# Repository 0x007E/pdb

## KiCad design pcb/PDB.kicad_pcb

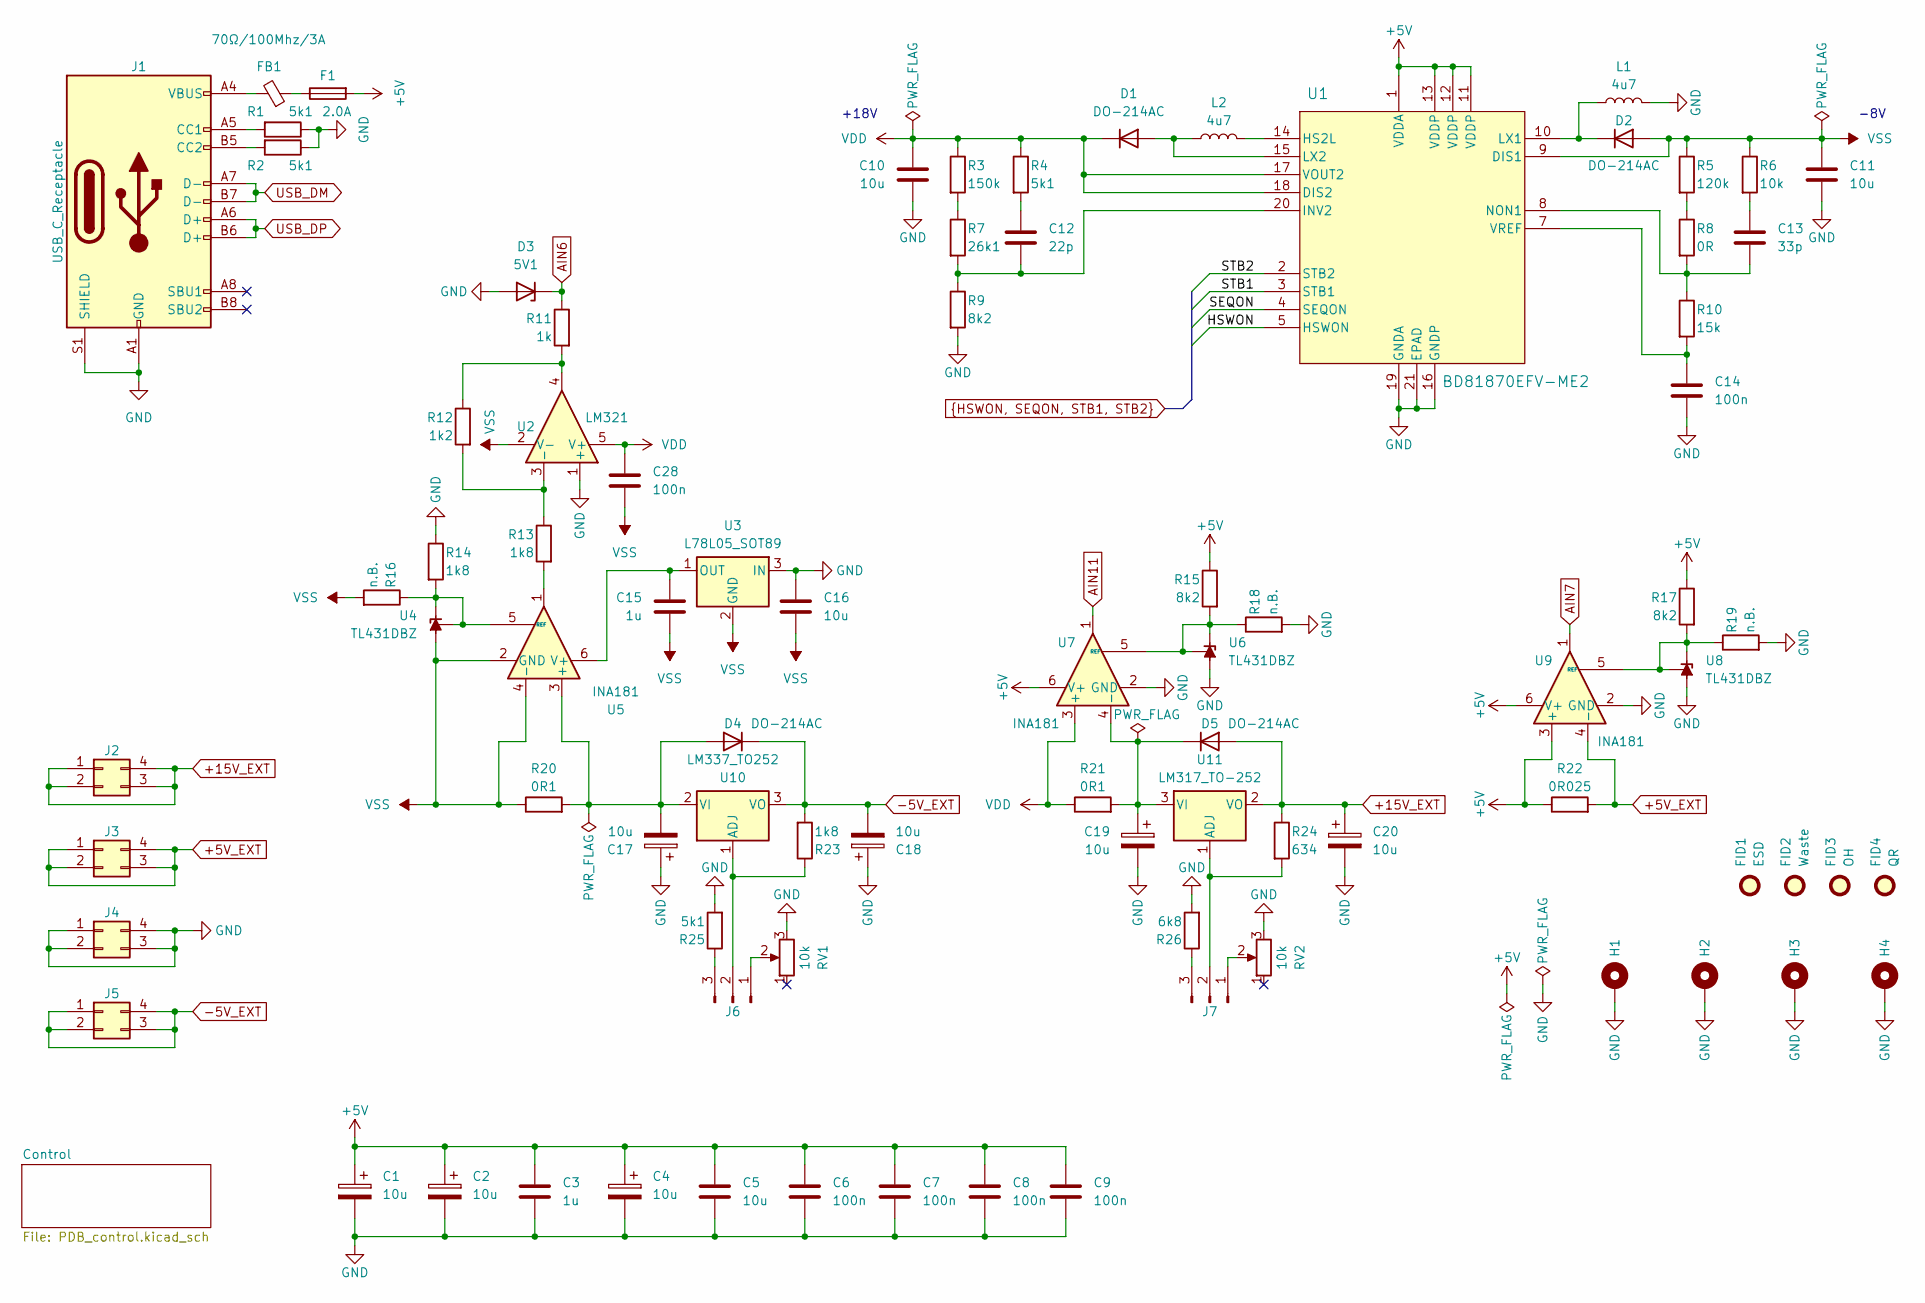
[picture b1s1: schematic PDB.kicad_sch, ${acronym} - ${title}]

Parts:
C1, C2, C4, C17, C18, C19, C20: 10u; CP_Elec_6.3x5.9; DigiKey 732-8545-1-ND
C3, C15: 1u; C_1206_3216Metric
C5, C10, C11, C16: 10u; C_1206_3216Metric
C6, C7, C8, C9, C14, C28: 100n; C_1206_3216Metric
C12: 22p; C_1206_3216Metric
C13: 33p; C_1206_3216Metric
D1, D2, D4, D5: DO-214AC; D_SMA
D3: 5V1; D_MiniMELF
F1: 2.0A; Fuse_1206_3216Metric
FB1: 70Ω/100Mhz/3A; L_1206_3216Metric
FID1: ESD; ESD-Logo_6.6x6mm_SilkScreen
FID2: Waste; WEEE-Logo_4.2x6mm_SilkScreen
FID3: OH; OSHW-Logo_5.7x6mm_SilkScreen
FID4: QR; QR_0x007e
H1, H2, H3, H4: MountingHole_Pad; MountingHole_3.2mm_M3_Pad
J1: USB_C_Receptacle; USB_C_Receptacle_GCT_USB4110
J2, J3, J4, J5: Conn_02x02_Counter_Clockwise; PinSocket_2x02_P2.54mm_Vertical; DigiKey 2057-RS2-04-G-ND
J6, J7: Conn_01x03_Pin; PinHeader_1x03_P2.54mm_Vertical
L1, L2: 4u7; L_Taiyo-Yuden_NR-40xx; DigiKey 587-2893-1-ND
R1, R2, R4, R25: 5k1; R_1206_3216Metric
R3: 150k; R_1206_3216Metric
R5: 120k; R_1206_3216Metric
R6: 10k; R_1206_3216Metric
R7: 26k1; R_1206_3216Metric
R8: 0R; R_1206_3216Metric
R9, R15, R17: 8k2; R_1206_3216Metric
R10: 15k; R_1206_3216Metric
R11: 1k; R_1206_3216Metric
R12: 1k2; R_1206_3216Metric
R13, R14, R23: 1k8; R_1206_3216Metric
R16, R18, R19: n.B.; R_1206_3216Metric
R20, R21: 0R1; R_2010_5025Metric; DigiKey CRM2010-FX-R100ELFCT-ND
R22: 0R025; R_2010_5025Metric
R24: 634; R_1206_3216Metric
R26: 6k8; R_1206_3216Metric
RV1, RV2: 10k; Potentiometer_Bourns_3296W_Vertical
U1: BD81870EFV-ME2; HTSSOP-20-1EP_4.4x6.5mm_P0.65mm_EP2.85x4mm; DigiKey BD81870EFV-ME2CT-ND
U2: LM321; SOT-23-5; DigiKey LM321SN3T1GOSCT-ND
U3: L78L05_SOT89; SOT-89-3
U4, U6, U8: TL431DBZ; SOT-23; DigiKey 5399-TL431CT-ND
U5, U7, U9: INA181; SOT-23-6
U10: LM337_TO252; TO-252-2; DigiKey 296-21578-1-ND
U11: LM317_TO-252; TO-252-2; DigiKey 5272-LM317MDT-EVCT-ND

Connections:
+5V: C1.1, C2.1, C3.1, C4.1, C5.1, C6.1, C7.1, C8.1, C9.1, F1.2, R15.1, R17.1, R22.1, U1.1 (VDDA), U1.11 (VDDP), U1.12 (VDDP), U1.13 (VDDP), U7.6 (V+), U9.3 (+), U9.6 (V+); also elsewhere on the board
+5V_EXT: J3.1, J3.2, J3.3, J3.4, R22.2, U9.4 (-); also elsewhere on the board
+15V_EXT: C20.1, D5.2 (A), J2.1, J2.2, J2.3, J2.4, R24.1, U11.2 (VO); also elsewhere on the board
-5V_EXT: C18.2, D4.1 (K), J5.1, J5.2, J5.3, J5.4, R23.2, U10.3 (VO); also elsewhere on the board
AIN6: D3.1 (K), R11.1; also elsewhere on the board
AIN7: U9.1; also elsewhere on the board
AIN11: U7.1; also elsewhere on the board
GND: C1.2, C2.2, C3.2, C4.2, C5.2, C6.2, C7.2, C8.2, C9.2, C10.1, C11.1, C14.1, C16.2, C17.1, C18.1, C19.2, C20.2, D3.2 (A), H1.1, H2.1, H3.1, H4.1, J1.A1 (GND), J1.A12 (GND), J1.B1 (GND), J1.B12 (GND), J1.S1 (SHIELD), J4.1, J4.2, J4.3, J4.4, L1.2, R1.1, R2.1, R9.2, R14.1, R18.2, R19.2, R25.2, R26.2, RV1.3, RV2.3, U1.16 (GNDP), U1.19 (GNDA), U1.21 (EPAD), U2.1 (+), U3.3 (IN), U6.3 (A), U7.2 (GND), U8.3 (A), U9.2 (GND); also elsewhere on the board
HSWON: U1.5 (HSWON); also elsewhere on the board
unnamed: C12.1, R4.2
unnamed: C13.2, R6.2
unnamed: D1.2 (A), L2.1, U1.15 (LX2)
unnamed: D2.1 (K), L1.1, U1.10 (LX1)
unnamed: C17.2, D4.2 (A), R20.2, U5.3 (+), U10.2 (VI)
unnamed: C19.1, D5.1 (K), R21.2, U7.4 (-), U11.3 (VI)
unnamed: F1.1, FB1.1
unnamed: FB1.2, J1.A4 (VBUS), J1.A9 (VBUS), J1.B4 (VBUS), J1.B9 (VBUS)
unnamed: J1.A5 (CC1), R1.2
unnamed: J1.B5 (CC2), R2.2
unnamed: J6.1, RV1.2
unnamed: J6.2, R23.1, U10.1 (ADJ)
unnamed: J6.3, R25.1
unnamed: J7.1, RV2.2
unnamed: J7.2, R24.2, U11.1 (ADJ)
unnamed: J7.3, R26.1
unnamed: R3.2, R7.1
unnamed: R5.2, R8.1
unnamed: R11.2, R12.1, U2.4
unnamed: R13.2, U5.1
unnamed: L2.2, U1.14 (HS2L)
unnamed: C12.2, R7.2, R9.1, U1.20 (INV2)
unnamed: C13.1, R8.2, R10.1, U1.8 (NON1)
unnamed: C14.2, R10.2, U1.7 (VREF)
unnamed: R12.2, R13.1, U2.3 (-)
unnamed: C15.2, U3.1 (OUT), U5.6 (V+)
unnamed: R14.2, R16.1, U4.1 (K), U4.2 (REF), U5.5 (REF)
unnamed: R15.2, R18.1, U6.1 (K), U6.2 (REF), U7.5 (REF)
unnamed: R17.2, R19.1, U8.1 (K), U8.2 (REF), U9.5 (REF)
SEQON: U1.4 (SEQON); also elsewhere on the board
STB1: U1.3 (STB1); also elsewhere on the board
STB2: U1.2 (STB2); also elsewhere on the board
USB_DM: J1.A7 (D-), J1.B7 (D-); also elsewhere on the board
USB_DP: J1.A6 (D+), J1.B6 (D+); also elsewhere on the board
VDD: C10.2, C28.1, D1.1 (K), R3.1, R4.1, R21.1, U1.17 (VOUT2), U1.18 (DIS2), U2.5 (V+), U7.3 (+)
VSS: C11.2, C15.1, C16.1, C28.2, D2.2 (A), R5.1, R6.1, R16.2, R20.1, U1.9 (DIS1), U2.2 (V-), U3.2 (GND), U4.3 (A), U5.2 (GND), U5.4 (-)

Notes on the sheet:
-8V
+18V

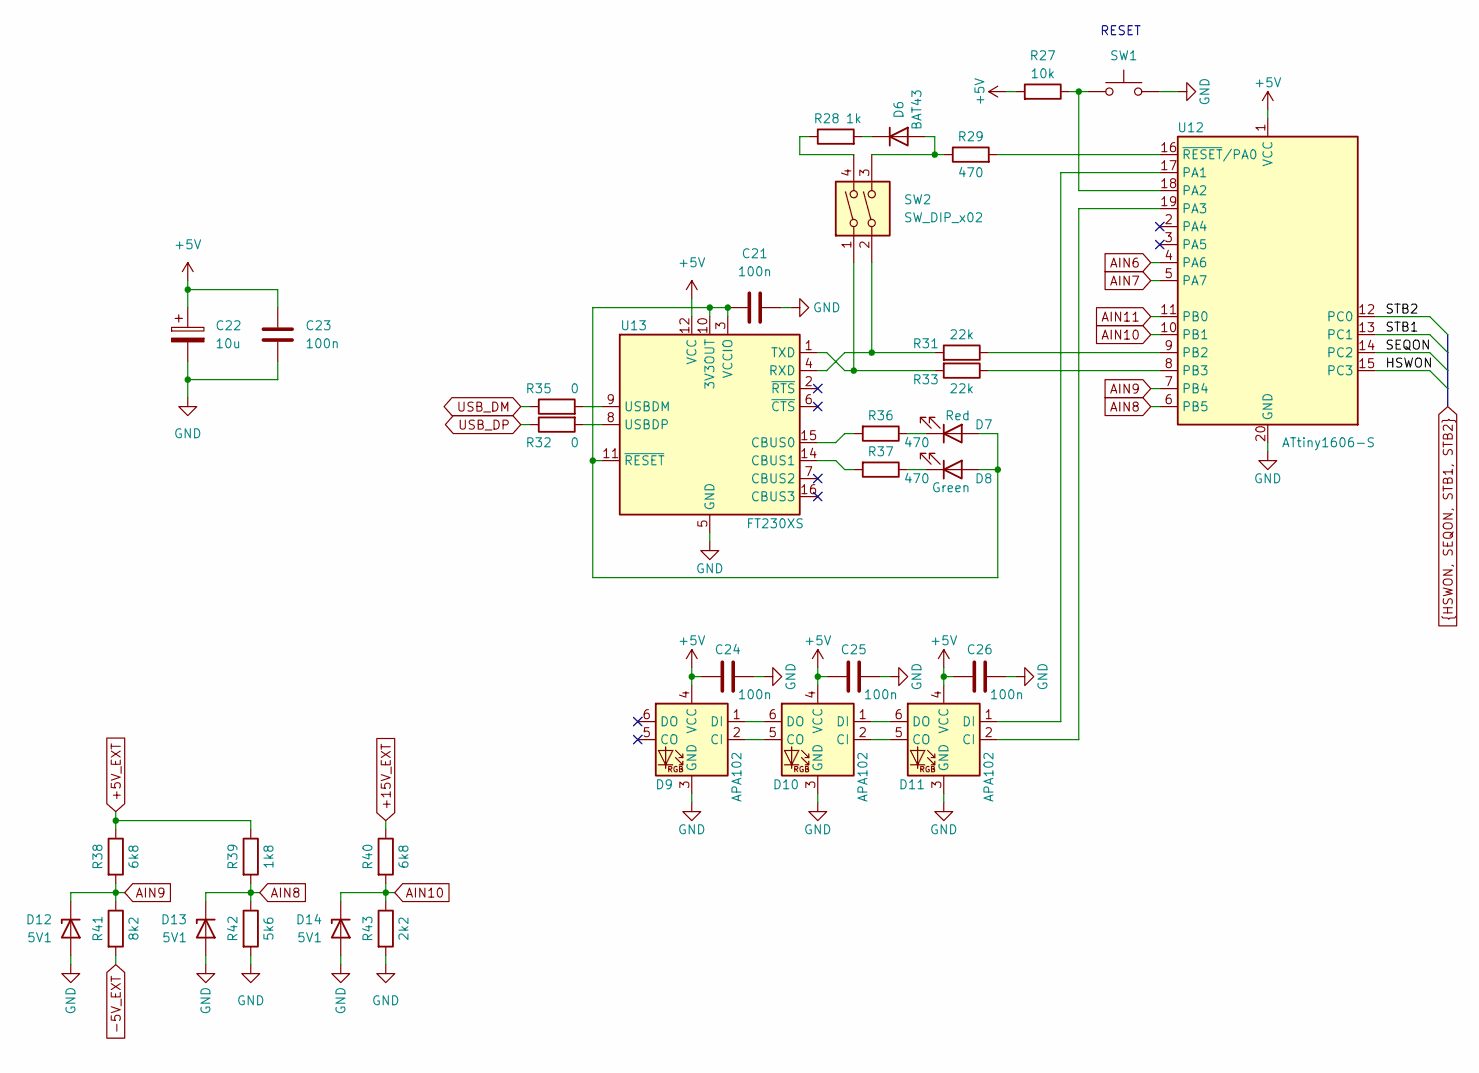
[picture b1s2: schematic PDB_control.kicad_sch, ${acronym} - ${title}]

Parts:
C21, C23, C24, C25, C26: 100n; C_1206_3216Metric
C22: 10u; CP_EIA-3528-21_Kemet-B
D6: BAT43; D_MiniMELF
D7: Red; LED_1206_3216Metric
D8: Green; LED_1206_3216Metric
D9, D10, D11: APA102; LED_RGB_5050-6
D12, D13, D14: 5V1; D_MiniMELF
R27: 10k; R_1206_3216Metric
R28: 1k; R_1206_3216Metric
R29, R36, R37: 470; R_1206_3216Metric
R31, R33: 22k; R_1206_3216Metric
R32, R35: 0; R_0603_1608Metric; DigiKey RMCF0603ZT0R00CT-ND
R38, R40: 6k8; R_1206_3216Metric
R39: 1k8; R_1206_3216Metric
R41: 8k2; R_1206_3216Metric
R42: 5k6; R_1206_3216Metric
R43: 2k2; R_1206_3216Metric
SW1: SW_Push; SW_SPST_PTS645
SW2: SW_DIP_x02; SW_DIP_SPSTx02_Slide_6.7x6.64mm_W8.61mm_P2.54mm_LowProfile
U12: ATtiny1606-S; SOIC-20W_7.5x12.8mm_P1.27mm
U13: FT230XS; SSOP-16_3.9x4.9mm_P0.635mm

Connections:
+5V: C22.1, C23.1, C24.2, C25.2, C26.2, D9.4 (VCC), D10.4 (VCC), D11.4 (VCC), R27.2, U12.1 (VCC), U13.12 (VCC); also elsewhere on the board
+5V_EXT: R38.1, R39.1; also elsewhere on the board
+15V_EXT: R40.1; also elsewhere on the board
-5V_EXT: R41.2; also elsewhere on the board
AIN6: U12.4 (PA6); also elsewhere on the board
AIN7: U12.5 (PA7); also elsewhere on the board
AIN8: D13.1 (K), R39.2, R42.1, U12.6 (PB5)
AIN9: D12.1 (K), R38.2, R41.1, U12.7 (PB4)
AIN10: D14.1 (K), R40.2, R43.1, U12.10 (PB1)
AIN11: U12.11 (PB0); also elsewhere on the board
GND: C21.2, C22.2, C23.2, C24.1, C25.1, C26.1, D9.3 (GND), D10.3 (GND), D11.3 (GND), D12.2 (A), D13.2 (A), D14.2 (A), R42.2, R43.2, SW1.1, U12.20 (GND), U13.5 (GND), U13.13 (GND); also elsewhere on the board
HSWON: U12.15 (PC3); also elsewhere on the board
unnamed: D6.2 (A), R29.1, SW2.3
unnamed: D6.1 (K), R28.2
unnamed: C21.1, D7.2 (A), D8.2 (A), U13.3 (VCCIO), U13.10 (3V3OUT), U13.11 (~RESET)
unnamed: D7.1 (K), R36.1
unnamed: D8.1 (K), R37.1
unnamed: D10.2 (CI), D11.5 (CO)
unnamed: D9.2 (CI), D10.5 (CO)
unnamed: D10.1 (DI), D11.6 (DO)
unnamed: D9.1 (DI), D10.6 (DO)
unnamed: D11.2 (CI), U12.19 (PA3)
unnamed: D11.1 (DI), U12.17 (PA1)
unnamed: R28.1, SW2.4
unnamed: R27.1, SW1.2, U12.18 (PA2)
unnamed: R31.1, U12.9 (PB2)
unnamed: R33.1, U12.8 (PB3)
unnamed: R29.2, U12.16 (~RESET/PA0)
unnamed: R36.2, U13.15 (CBUS0)
unnamed: R37.2, U13.14 (CBUS1)
unnamed: R31.2, SW2.2, U13.4 (RXD)
unnamed: R33.2, SW2.1, U13.1 (TXD)
unnamed: R35.2, U13.9 (USBDM)
unnamed: R32.2, U13.8 (USBDP)
SEQON: U12.14 (PC2); also elsewhere on the board
STB1: U12.13 (PC1); also elsewhere on the board
STB2: U12.12 (PC0); also elsewhere on the board
USB_DM: R35.1; also elsewhere on the board
USB_DP: R32.1; also elsewhere on the board

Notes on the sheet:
RESET

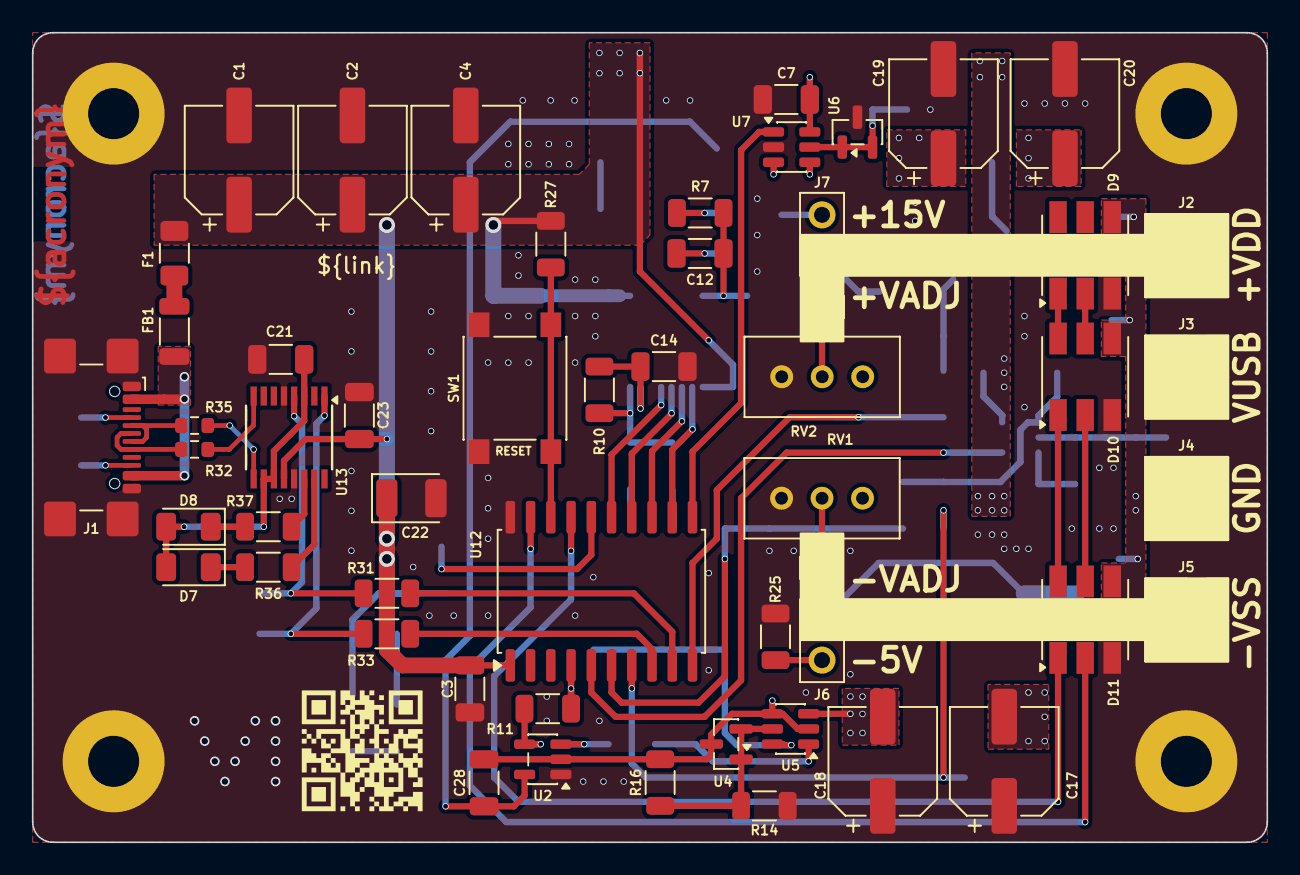
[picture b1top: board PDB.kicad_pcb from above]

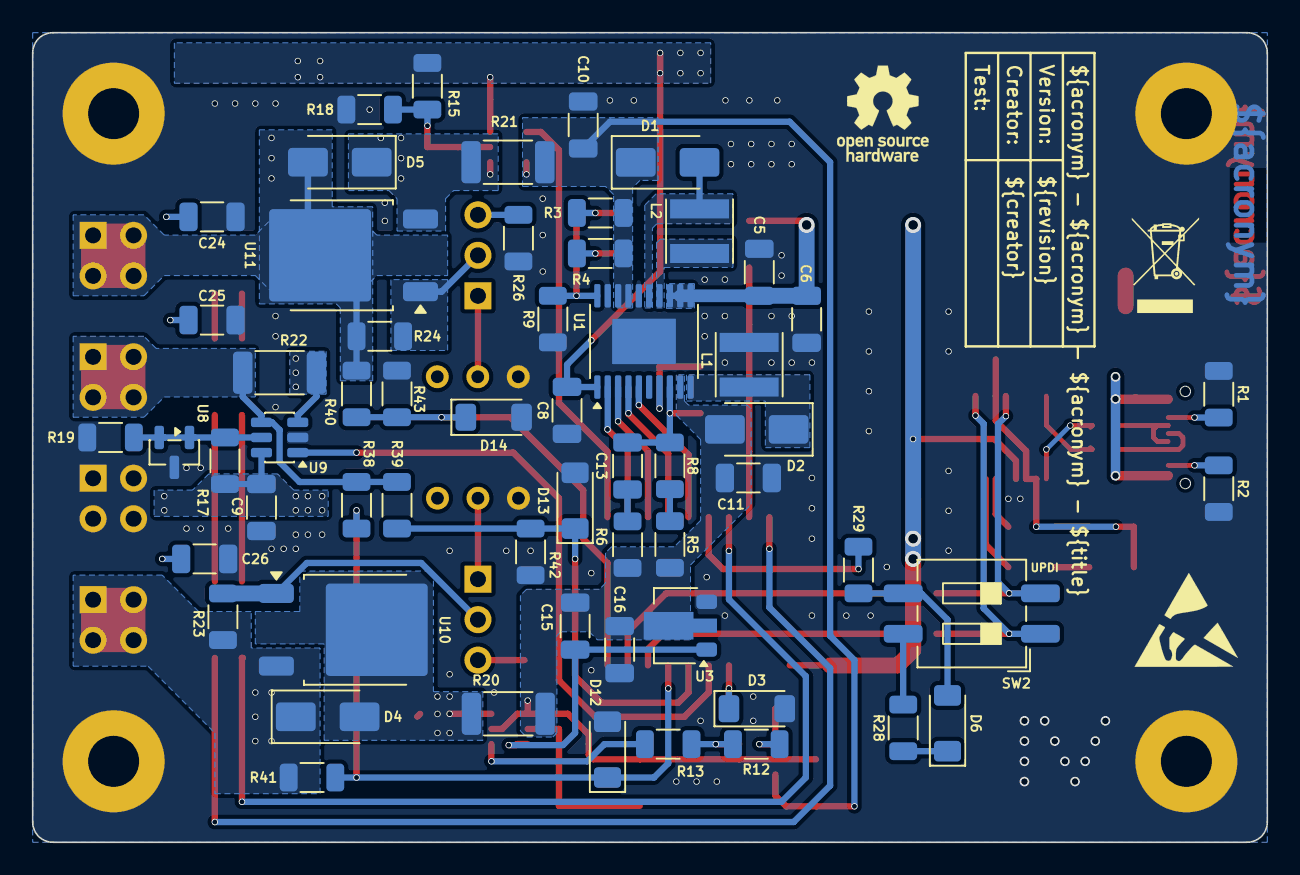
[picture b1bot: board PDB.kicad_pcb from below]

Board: 2 copper layers, 77.5 x 50.8 mm, 118 parts (61 on the bottom side), 70 nets.

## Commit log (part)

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2026-05-04 Add pcb layout
2026-05-05 Add mechanical parts
2026-05-27 Update to KiCAD 9
2026-05-27 Add build pipeline
2026-05-27 Add dimensioning
2026-05-27 Add release pipeline
2026-06-04 Change MCP2221A to FT230X
2026-06-05 Optimize +3V3 signal

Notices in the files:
parts and their libraries:
license: CC BY-NC-SA 4.0
